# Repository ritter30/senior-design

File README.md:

# G.A.I.N.S Team 19
Cameron Williams \
Max Ritter \
Mark Melvin \
Aidan Leib

## Documentation

All documentation for the project is located in [`./docs`](./docs/).

Hyperlinks to frequently used:

- [Git Commands Cheat Sheet](./docs/git_cheatsheet.md)
- etc...

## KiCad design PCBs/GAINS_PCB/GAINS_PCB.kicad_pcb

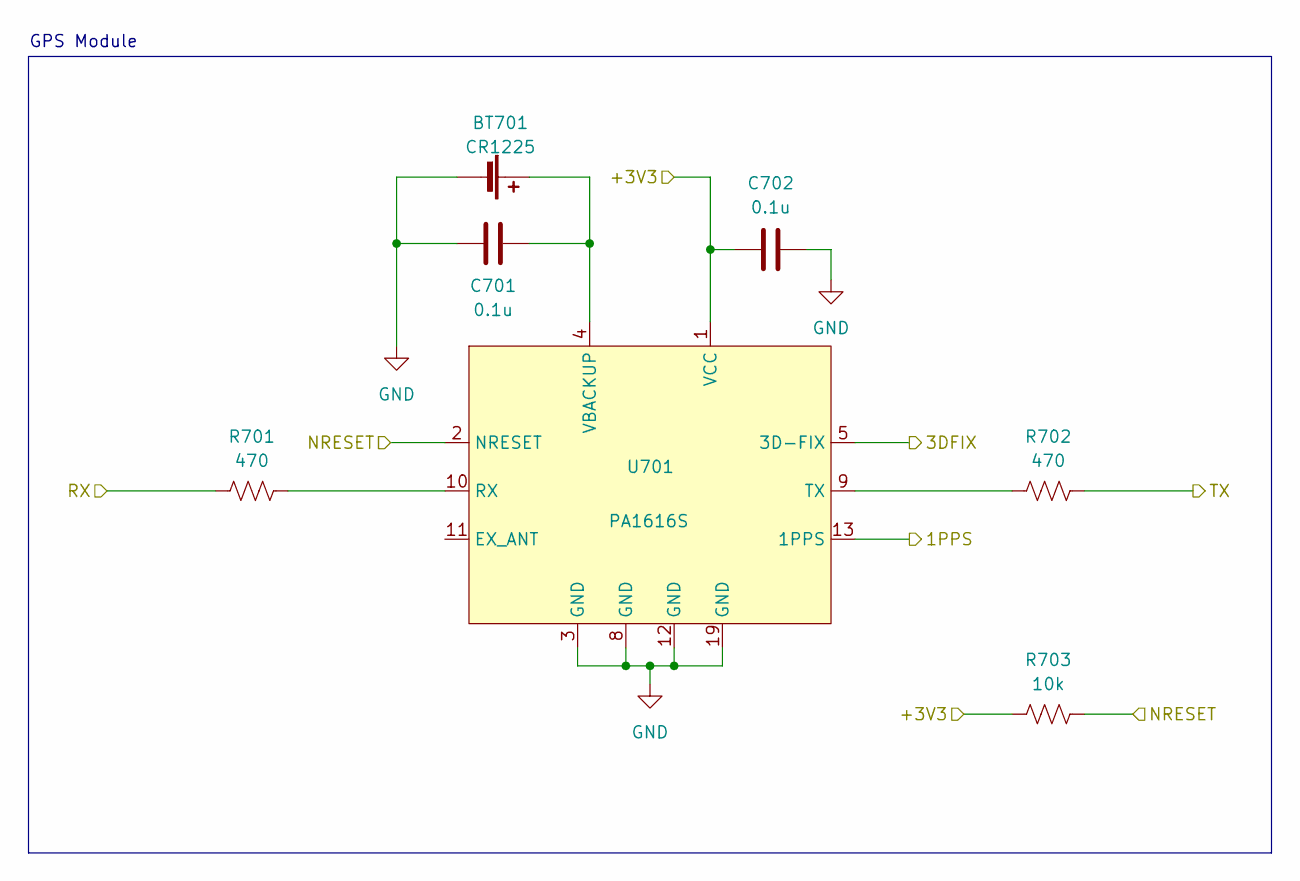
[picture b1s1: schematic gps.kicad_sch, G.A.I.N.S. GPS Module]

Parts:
BT701: CR1225; Battery_Panasonic_CR1220-VCN_Vertical_CircularHoles
C701, C702: 0.1u; C_0805_2012Metric_Pad1.18x1.45mm_HandSolder
R701, R702: 470; R_0805_2012Metric_Pad1.20x1.40mm_HandSolder
R703: 10k; R_0805_2012Metric_Pad1.20x1.40mm_HandSolder
U701: PA1616S

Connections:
/GPS/1PPS: U701.13 (1PPS); also elsewhere on the board
/GPS/3DFIX: U701.5 (3D-FIX); also elsewhere on the board
/GPS/+3V3: C702.1, R703.1, U701.1 (VCC); also elsewhere on the board
/GPS/NRESET: R703.2, U701.2 (NRESET); also elsewhere on the board
/GPS/RX: R701.1; also elsewhere on the board
/GPS/TX: R702.1; also elsewhere on the board
GND: BT701.2 (-), C701.1, C702.2, U701.3 (GND), U701.8 (GND), U701.12 (GND), U701.19 (GND); also elsewhere on the board
unnamed: BT701.1 (+), C701.2, U701.4 (VBACKUP)
unnamed: R701.2, U701.10 (RX)
unnamed: R702.2, U701.9 (TX)

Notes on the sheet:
GPS Module

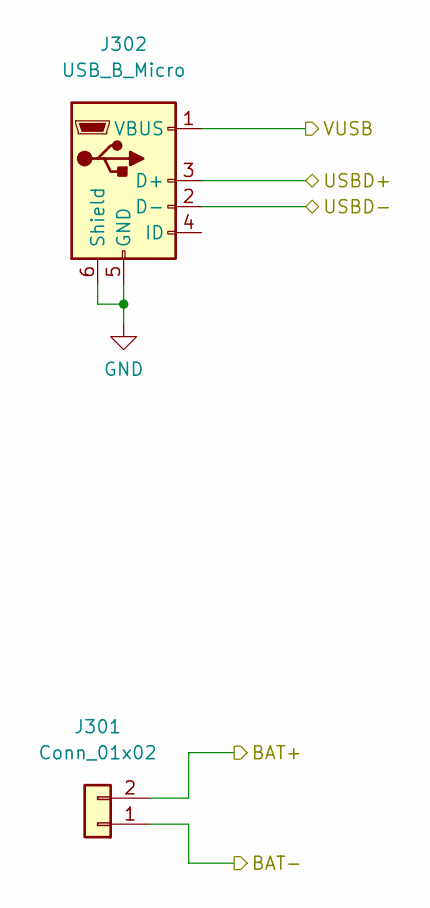
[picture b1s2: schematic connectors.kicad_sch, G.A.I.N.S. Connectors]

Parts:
J301: Conn_01x02; JST_GH_BM02B-GHS-TBT_1x02-1MP_P1.25mm_Vertical
J302: USB_B_Micro; USB_Micro-B_Amphenol_10104110_Horizontal

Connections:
/Connectors/BAT+: J301.2; also elsewhere on the board
/Connectors/BAT-: J301.1
/Connectors/USBD+: J302.3 (D+); also elsewhere on the board
/Connectors/USBD-: J302.2 (D-); also elsewhere on the board
/Connectors/VUSB: J302.1 (VBUS); also elsewhere on the board
GND: J302.5 (GND), J302.6 (Shield); also elsewhere on the board

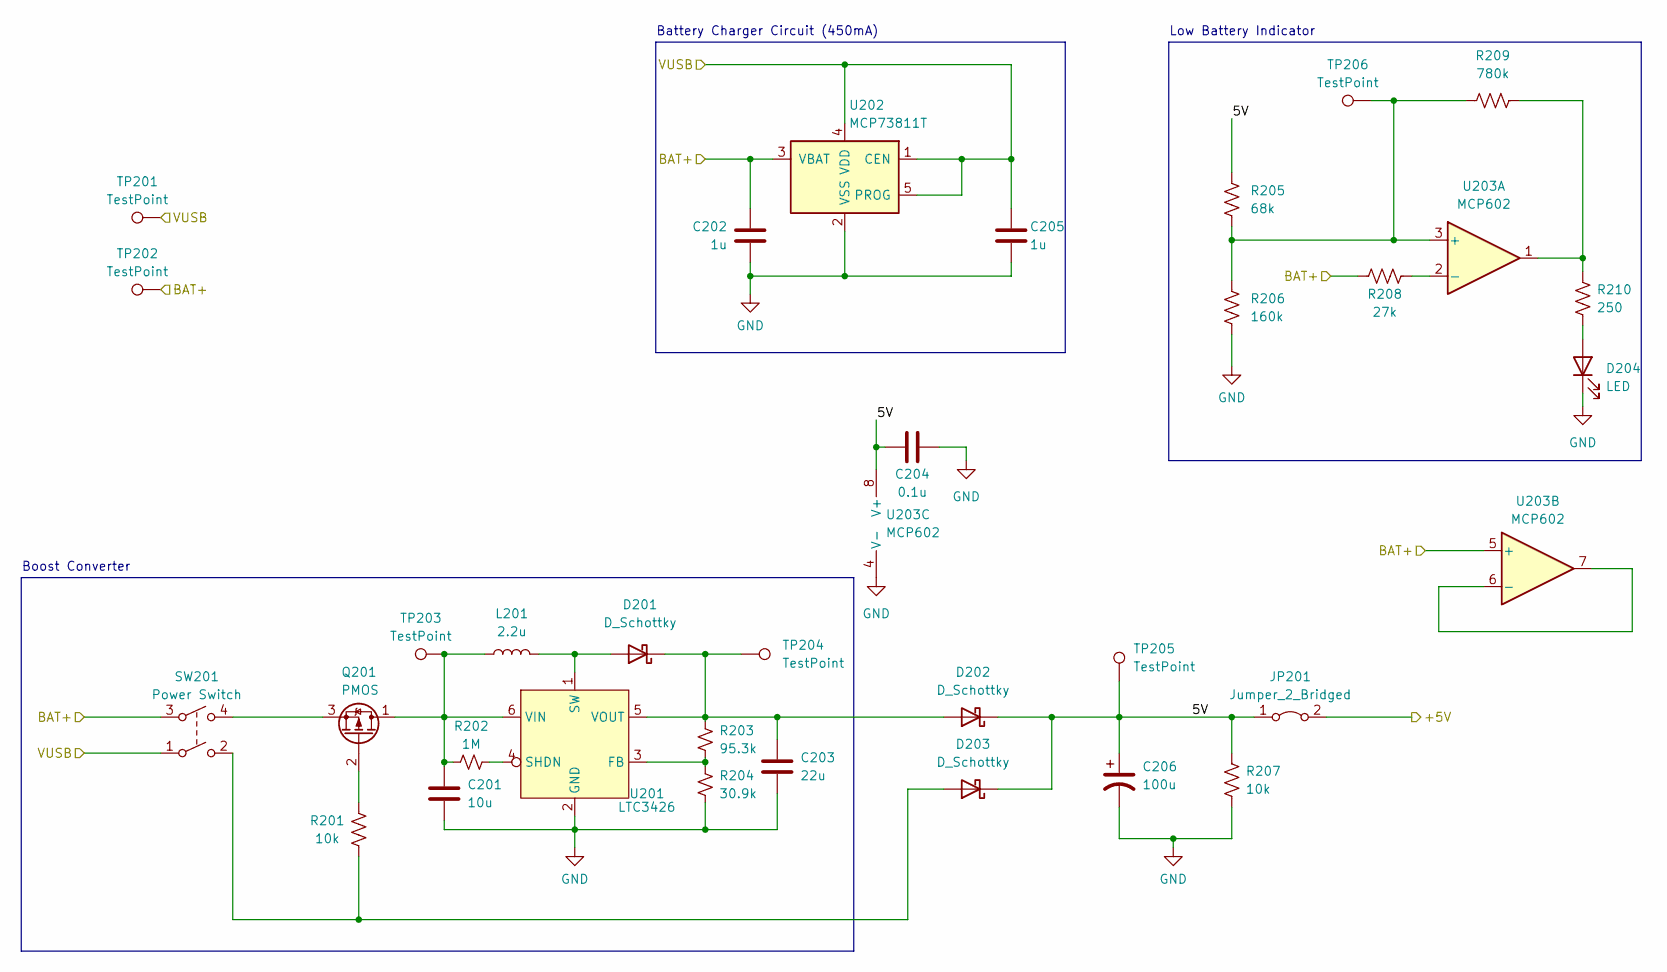
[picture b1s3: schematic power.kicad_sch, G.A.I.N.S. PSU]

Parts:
C201: 10u; C_0805_2012Metric_Pad1.18x1.45mm_HandSolder
C202, C205: 1u; C_0805_2012Metric_Pad1.18x1.45mm_HandSolder
C203: 22u; CP_Radial_D5.0mm_P2.00mm
C204: 0.1u; C_0805_2012Metric_Pad1.18x1.45mm_HandSolder
C206: 100u; CP_Radial_D10.0mm_P5.00mm
D201, D202, D203: D_Schottky; D_DO-41_SOD81_P10.16mm_Horizontal
D204: LED; LED_D5.0mm
JP201: Jumper_2_Bridged; SolderJumper-2_P1.3mm_Open_Pad1.0x1.5mm
L201: 2.2u; L_Radial_D8.7mm_P5.00mm_Fastron_07HCP
Q201: PMOS; TO-220-3_Vertical
R201, R207: 10k; R_0805_2012Metric_Pad1.20x1.40mm_HandSolder
R202: 1M; R_0805_2012Metric_Pad1.20x1.40mm_HandSolder
R203: 95.3k; R_0805_2012Metric_Pad1.20x1.40mm_HandSolder
R204: 30.9k; R_0805_2012Metric_Pad1.20x1.40mm_HandSolder
R205: 68k; R_0805_2012Metric_Pad1.20x1.40mm_HandSolder
R206: 160k; R_0805_2012Metric_Pad1.20x1.40mm_HandSolder
R208: 27k; R_0805_2012Metric_Pad1.20x1.40mm_HandSolder
R209: 780k; R_0805_2012Metric_Pad1.20x1.40mm_HandSolder
R210: 250; R_0805_2012Metric_Pad1.20x1.40mm_HandSolder
SW201: Power Switch
TP201, TP202, TP203, TP204, TP205, TP206: TestPoint; PinHeader_1x01_P1.27mm_Vertical
U201: LTC3426; TSOT-23-6_HandSoldering
U202: MCP73811T; SOT-23-5_HandSoldering
U203: MCP602; DIP-8_W7.62mm_Socket

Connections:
/Connectors/BAT+: C202.1, R208.1, SW201.3, TP202.1, U202.3 (VBAT), U203.5 (+); also elsewhere on the board
/Connectors/VUSB: C205.1, SW201.1, TP201.1, U202.1 (CEN), U202.4 (VDD), U202.5 (PROG); also elsewhere on the board
/Power/5V: C204.1, C206.1, D202.1 (K), D203.1 (K), JP201.1 (A), R205.2, R207.1, TP205.1, U203.8 (V+)
/Power/+5V: JP201.2 (B); also elsewhere on the board
GND: C201.2, C202.2, C203.2, C204.2, C205.2, C206.2, D204.1 (K), R204.2, R206.1, R207.2, U201.2 (GND), U202.2 (VSS), U203.4 (V-); also elsewhere on the board
unnamed: D201.2 (A), L201.2, U201.1 (SW)
unnamed: C203.1, D201.1 (K), D202.2 (A), R203.1, TP204.1, U201.5 (VOUT)
unnamed: D203.2 (A), R201.1, SW201.2
unnamed: D204.2 (A), R210.2
unnamed: C201.1, L201.1, Q201.1 (D), R202.1, TP203.1, U201.6 (VIN)
unnamed: Q201.2 (G), R201.2
unnamed: Q201.3 (S), SW201.4
unnamed: R209.2, R210.1, U203.1
unnamed: R203.2, R204.1, U201.3 (FB)
unnamed: R202.2, U201.4 (SHDN)
unnamed: R205.1, R206.2, R209.1, TP206.1, U203.3 (+)
unnamed: R208.2, U203.2 (-)
unnamed: U203.6 (-), U203.7

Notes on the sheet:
Boost Converter
Low Battery Indicator
Battery Charger Circuit (450mA)

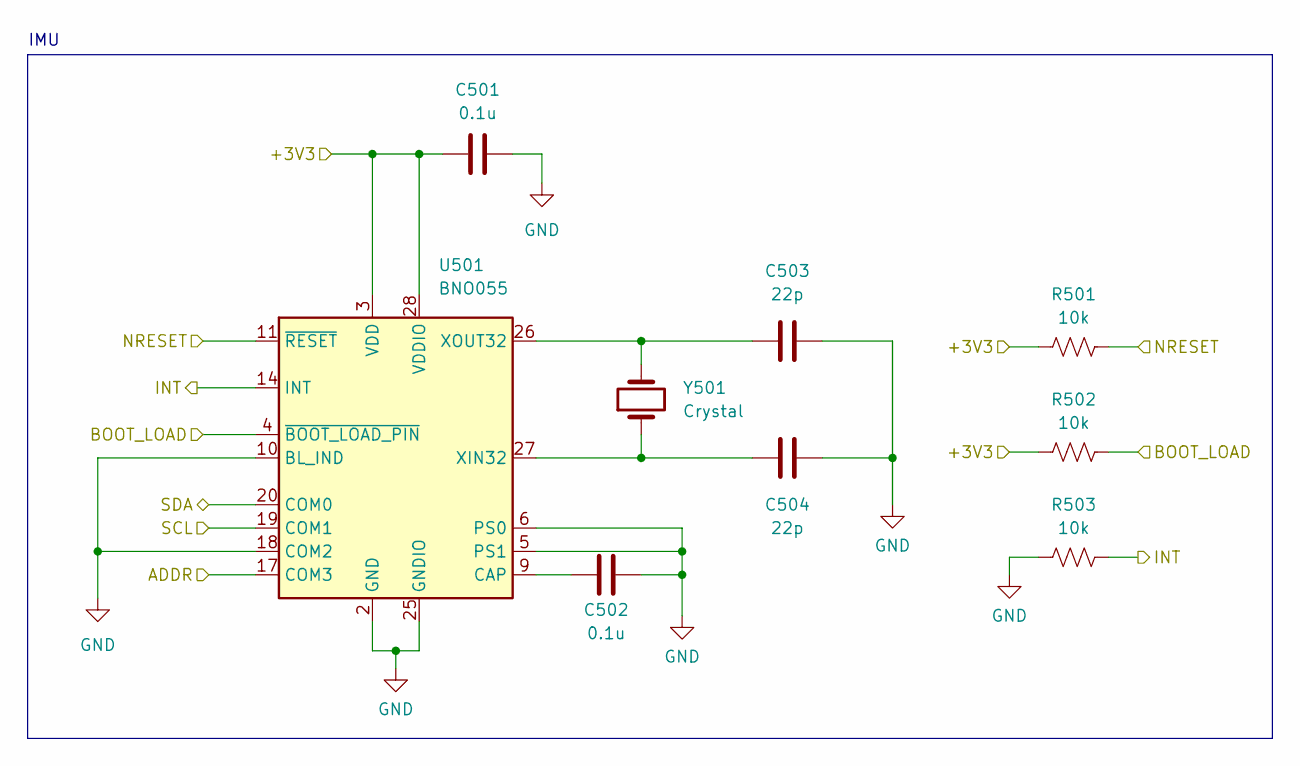
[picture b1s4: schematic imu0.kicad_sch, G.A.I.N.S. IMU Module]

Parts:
C501, C502: 0.1u; C_0805_2012Metric_Pad1.18x1.45mm_HandSolder
C503, C504: 22p; C_0805_2012Metric_Pad1.18x1.45mm_HandSolder
R501, R502, R503: 10k; R_0805_2012Metric_Pad1.20x1.40mm_HandSolder
U501: BNO055; LGA-28_5.2x3.8mm_P0.5mm
Y501: Crystal; Crystal_DS26_D2.0mm_L6.0mm_Vertical

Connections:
/GPS/+3V3: C501.1, R501.1, R502.1, U501.3 (VDD), U501.28 (VDDIO); also elsewhere on the board
/IMU0/BOOT_LOAD: R502.2, U501.4 (~BOOT_LOAD_PIN); also elsewhere on the board
/IMU0/INT: R503.2, U501.14 (INT); also elsewhere on the board
/IMU0/NRESET: R501.2, U501.11 (~RESET); also elsewhere on the board
/IMU0/SCL: U501.19 (COM1); also elsewhere on the board
/IMU0/SDA: U501.20 (COM0); also elsewhere on the board
GND: C501.2, C502.2, C503.1, C504.1, R503.1, U501.2 (GND), U501.5 (PS1), U501.6 (PS0), U501.10 (BL_IND), U501.15 (GNDIO), U501.16 (GNDIO), U501.18 (COM2), U501.25 (GNDIO); also elsewhere on the board
unnamed: C502.1, U501.9 (CAP)
unnamed 45: U501.17 (COM3); also elsewhere on the board
unnamed: C504.2, U501.27 (XIN32), Y501.1
unnamed: C503.2, U501.26 (XOUT32), Y501.2

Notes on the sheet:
IMU

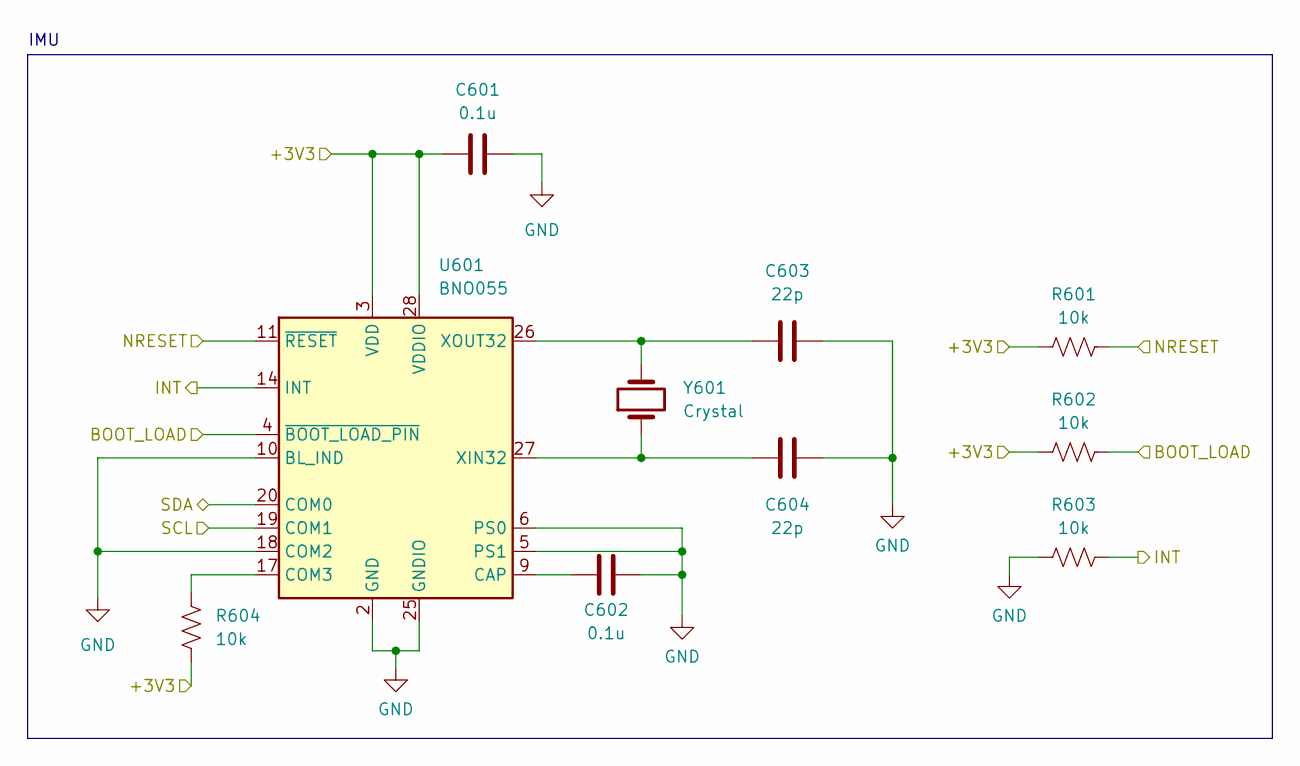
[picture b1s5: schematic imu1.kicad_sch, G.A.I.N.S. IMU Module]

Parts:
C601, C602: 0.1u; C_0805_2012Metric_Pad1.18x1.45mm_HandSolder
C603, C604: 22p; C_0805_2012Metric_Pad1.18x1.45mm_HandSolder
R601, R602, R603, R604: 10k; R_0805_2012Metric_Pad1.20x1.40mm_HandSolder
U601: BNO055; LGA-28_5.2x3.8mm_P0.5mm
Y601: Crystal; Crystal_DS26_D2.0mm_L6.0mm_Vertical

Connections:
/GPS/+3V3: C601.1, R601.1, R602.1, R604.2, U601.3 (VDD), U601.28 (VDDIO); also elsewhere on the board
/IMU0/SCL: U601.19 (COM1); also elsewhere on the board
/IMU0/SDA: U601.20 (COM0); also elsewhere on the board
/IMU1/BOOT_LOAD: R602.2, U601.4 (~BOOT_LOAD_PIN); also elsewhere on the board
/IMU1/INT: R603.2, U601.14 (INT); also elsewhere on the board
/IMU1/NRESET: R601.2, U601.11 (~RESET); also elsewhere on the board
GND: C601.2, C602.2, C603.1, C604.1, R603.1, U601.2 (GND), U601.5 (PS1), U601.6 (PS0), U601.10 (BL_IND), U601.15 (GNDIO), U601.16 (GNDIO), U601.18 (COM2), U601.25 (GNDIO); also elsewhere on the board
unnamed: C602.1, U601.9 (CAP)
unnamed: R604.1, U601.17 (COM3)
unnamed: C604.2, U601.27 (XIN32), Y601.1
unnamed: C603.2, U601.26 (XOUT32), Y601.2

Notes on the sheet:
IMU

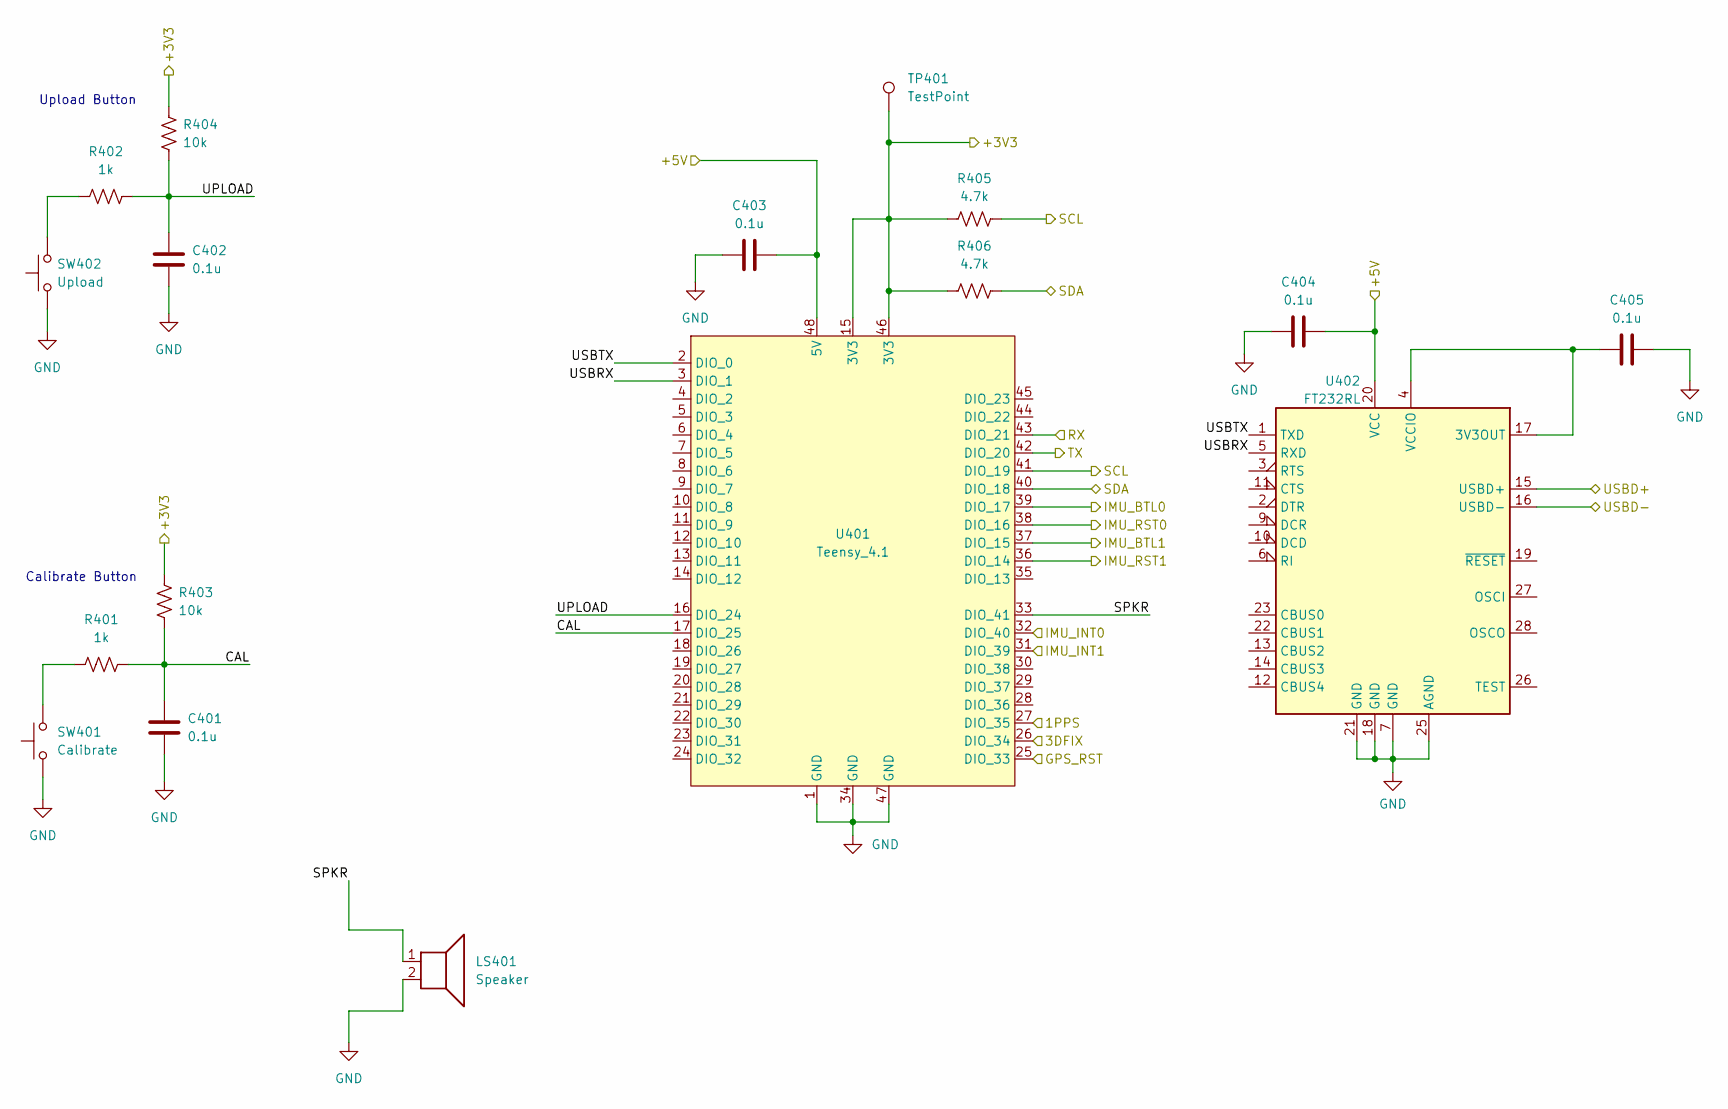
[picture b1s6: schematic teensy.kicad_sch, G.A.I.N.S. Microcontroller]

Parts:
C401, C402, C403, C404, C405: 0.1u; C_0805_2012Metric_Pad1.18x1.45mm_HandSolder
LS401: Speaker; Buzzer_12x9.5RM7.6
R401, R402: 1k; R_0805_2012Metric_Pad1.20x1.40mm_HandSolder
R403, R404: 10k; R_0805_2012Metric_Pad1.20x1.40mm_HandSolder
R405, R406: 4.7k; R_0805_2012Metric_Pad1.20x1.40mm_HandSolder
SW401: Calibrate; SW_PUSH_6mm
SW402: Upload; SW_PUSH_6mm
TP401: TestPoint; PinHeader_1x01_P1.27mm_Vertical
U401: Teensy_4.1; Teensy41
U402: FT232RL; SSOP-28_5.3x10.2mm_P0.65mm

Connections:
/Connectors/USBD+: U402.15 (USBD+); also elsewhere on the board
/Connectors/USBD-: U402.16 (USBD-); also elsewhere on the board
/GPS/1PPS: U401.27 (DIO_35); also elsewhere on the board
/GPS/3DFIX: U401.26 (DIO_34); also elsewhere on the board
/GPS/+3V3: R403.1, R404.1, R405.1, R406.1, TP401.1, U401.15 (3V3), U401.46 (3V3); also elsewhere on the board
/GPS/NRESET: U401.25 (DIO_33); also elsewhere on the board
/GPS/RX: U401.42 (DIO_20); also elsewhere on the board
/GPS/TX: U401.43 (DIO_21); also elsewhere on the board
/IMU0/BOOT_LOAD: U401.39 (DIO_17); also elsewhere on the board
/IMU0/INT: U401.32 (DIO_40); also elsewhere on the board
/IMU0/NRESET: U401.38 (DIO_16); also elsewhere on the board
/IMU0/SCL: R405.2, U401.41 (DIO_19); also elsewhere on the board
/IMU0/SDA: R406.2, U401.40 (DIO_18); also elsewhere on the board
/IMU1/BOOT_LOAD: U401.37 (DIO_15); also elsewhere on the board
/IMU1/INT: U401.31 (DIO_39); also elsewhere on the board
/IMU1/NRESET: U401.36 (DIO_14); also elsewhere on the board
/Power/+5V: C403.2, C404.1, U401.48 (5V), U402.20 (VCC); also elsewhere on the board
/Teensy/CAL: C401.1, R401.2, R403.2, U401.17 (DIO_25)
/Teensy/SPKR: LS401.1, U401.33 (DIO_41)
/Teensy/UPLOAD: C402.1, R402.2, R404.2, U401.16 (DIO_24)
/Teensy/USBRX: U401.3 (DIO_1), U402.5 (RXD)
/Teensy/USBTX: U401.2 (DIO_0), U402.1 (TXD)
GND: C401.2, C402.2, C403.1, C404.2, C405.1, LS401.2, SW401.1, SW402.1, U401.1 (GND), U401.34 (GND), U401.47 (GND), U402.7 (GND), U402.18 (GND), U402.21 (GND), U402.25 (AGND); also elsewhere on the board
unnamed: R401.1, SW401.2
unnamed: R402.1, SW402.2
unnamed: C405.2, U402.4 (VCCIO), U402.17 (3V3OUT)

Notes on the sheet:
Calibrate Button
Upload Button

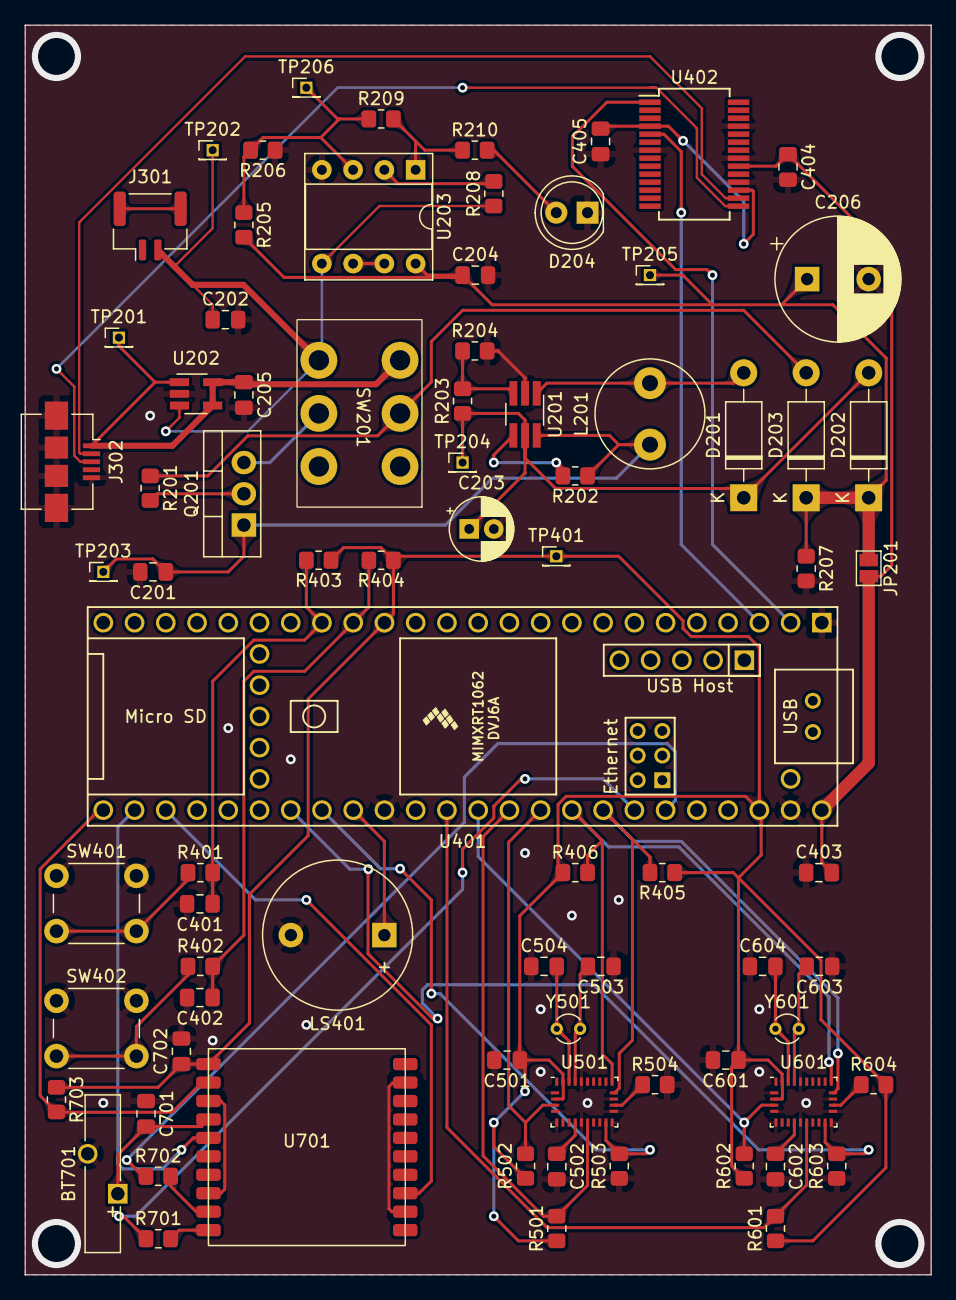
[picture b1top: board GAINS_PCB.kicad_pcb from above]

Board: 2 copper layers, 73.7 x 101.6 mm, 79 parts (0 on the bottom side), 53 nets.

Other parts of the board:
R504: 10k; R_0805_2012Metric_Pad1.20x1.40mm_HandSolder

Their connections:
GND: R504.2; also elsewhere on the board
unnamed 45: R504.1; also elsewhere on the board

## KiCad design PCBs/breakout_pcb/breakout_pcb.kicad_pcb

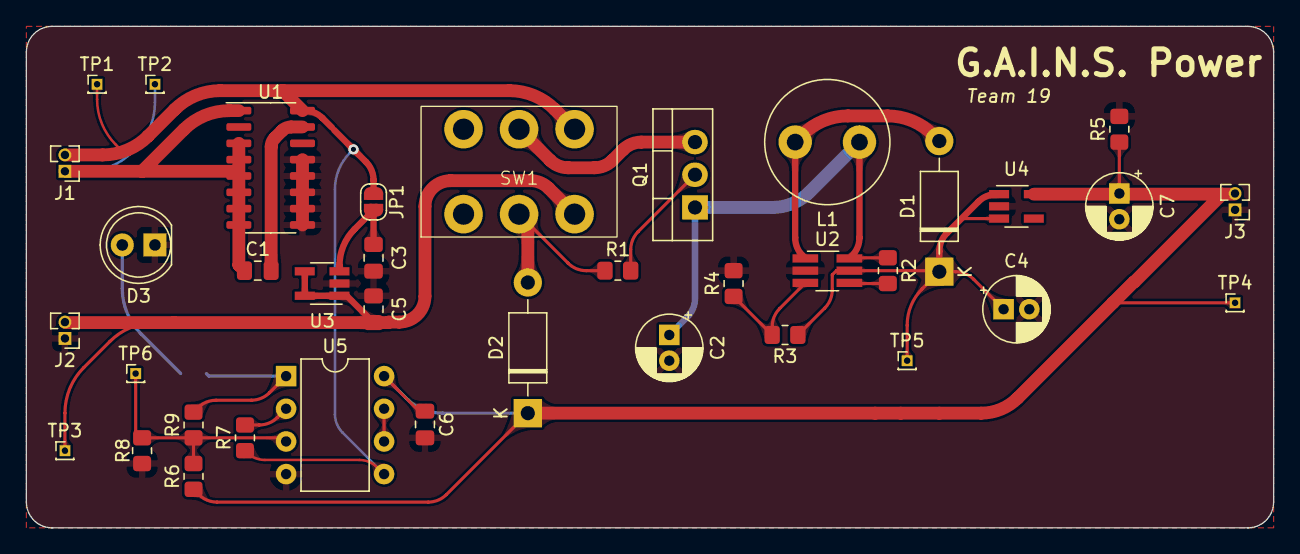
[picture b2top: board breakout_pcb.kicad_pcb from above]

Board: 2 copper layers, 97.0 x 39.0 mm, 38 parts (1 on the bottom side), 20 nets.

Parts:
C1, C6: 0.1u; C_0805_2012Metric_Pad1.18x1.45mm_HandSolder
C2: 10u; CP_Radial_D5.0mm_P2.00mm
C3, C5: 1u; C_0805_2012Metric_Pad1.18x1.45mm_HandSolder
C4: 22u; CP_Radial_D5.0mm_P2.00mm
C7: 82u; CP_Radial_D5.0mm_P2.00mm
D1, D2: 1N5819; D_DO-41_SOD81_P10.16mm_Horizontal
D3: Red LED; LED_D5.0mm
J1, J2, J3: Conn_01x02_Socket; PinHeader_1x02_P1.27mm_Vertical
JP1: Jumper_2_Open; SolderJumper-2_P1.3mm_Open_RoundedPad1.0x1.5mm
L1: 2.2u; L_Radial_D9.5mm_P5.00mm_Fastron_07HVP
Q1: IRF9630; TO-220-3_Vertical
R1, R5, R6: 10k; R_0805_2012Metric_Pad1.20x1.40mm_HandSolder
R2: 1M; R_0805_2012Metric_Pad1.20x1.40mm_HandSolder
R3: 95.3k; R_0805_2012Metric_Pad1.20x1.40mm_HandSolder
R4: 30.9k; R_0805_2012Metric_Pad1.20x1.40mm_HandSolder
R7: 1k; R_0805_2012Metric_Pad1.20x1.40mm_HandSolder
R8: 30k; R_0805_2012Metric_Pad1.20x1.40mm_HandSolder
R9: 100k; R_0805_2012Metric_Pad1.20x1.40mm_HandSolder
R10: 250; R_0805_2012Metric_Pad1.20x1.40mm_HandSolder
SW1: SW_DPST; Power Switch
TP1, TP2, TP3, TP4, TP5, TP6: TestPoint; PinHeader_1x01_P1.00mm_Vertical
U1: UCC39562; SOIC-16_3.9x9.9mm_P1.27mm
U2: LTC3426; TSOT-23-6_HandSoldering
U3: MCP73811T; SOT-23-5_HandSoldering
U4: MAX40200AUK; SOT-23-5_HandSoldering
U5: MCP602; DIP-8_W7.62mm

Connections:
/+5V: C6.1, C7.1, D2.1 (K), J3.2, R5.1, R6.1, TP4.1, U4.5 (OUT), U5.8 (V+)
/BAT+: J1.2, JP1.1 (A), R7.1, SW1.3, TP1.1, U1.16 (PACK+), U5.5 (+)
/BAT-: C1.1, J1.1, TP2.1, U1.1 (TCLK), U1.3 (BNEG), U1.4 (BNEG), U1.5 (BNEG), U1.6 (BNEG), U1.7 (BNEG), U1.8 (BNEG)
/VUSB: C5.1, J2.2, SW1.1, TP3.1, U3.1 (CEN), U3.4 (VDD), U3.5 (PROG)
GND: C2.2, C3.2, C4.2, C5.2, C6.2, C7.2, D3.1 (K), J2.1, J3.1, R4.2, R5.2, R8.2, U1.9 (PACK-), U1.10 (PACK-), U1.11 (PACK-), U1.12 (PACK-), U1.13 (PACK-), U2.2 (GND), U3.2 (VSS), U4.2 (GND), U5.4 (V-)
unnamed: D1.2 (A), L1.2, U2.1 (SW)
unnamed: C4.1, D1.1 (K), R3.1, TP5.1, U2.5 (VOUT), U4.1 (VDD), U4.3 (EN)
unnamed: D2.2 (A), R1.1, SW1.2
unnamed: D3.2 (A), R10.2
unnamed: C3.1, JP1.2 (B), U3.3 (VBAT)
unnamed: C2.1, L1.1, Q1.1 (D), R2.1, U2.6 (VIN)
unnamed: Q1.2 (G), R1.2
unnamed: Q1.3 (S), SW1.4
unnamed: R9.2, R10.1, U5.1
unnamed: C1.2, U1.15 (CBPS)
unnamed: R3.2, R4.1, U2.3 (FB)
unnamed: R2.2, U2.4 (SHDN)
unnamed: R6.2, R8.1, R9.1, TP6.1, U5.3 (+)
unnamed: R7.2, U5.2 (-)
unnamed: U5.6 (-), U5.7

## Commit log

2024-01-11 testing repo access
2024-01-11 test two for git scripting
2024-01-13 added mermaid.js code for the activity diagram
2024-01-25 added
2024-01-25 adding documentation
2024-01-25 Added PCB
2024-01-26 Initial PCB Schematic
2024-01-26 Teensy and IMU PCB Schematics
2024-01-28 PCB Schematic Updates
2024-01-30 minor changes
2024-01-30 updated git cheatsheet
2024-01-30 Fixing Schematic
2024-02-01 PCB Updates
2024-02-02 removing schematic from branch 'aidan'
2024-02-02 introduction to building the application, added styling files and data
2024-02-04 Micro code
2024-02-05 Attempting live data updates
2024-02-05 Working live update mvp App
2024-02-08 Updated battery protection circuit
2024-02-08 Added the breakout board PCB
2024-02-08 init for pyserial implementation
2024-02-08 almost forgot updated gitignore
2024-02-09 Worked on PCB
2024-02-09 updated power breakout board
2024-02-09 Final Breakout Board PCB
2024-02-09 updated .gitignore
2024-02-12 build gerber files for ordering PCB
2024-02-13 playing with plotting geospatial data
2024-02-14 negiligible updates to app
2024-02-14 updated gitignore
2024-02-15 pushing working tree, only changed app print()
2024-02-15 added kalman filter script to play with
2024-02-17 Deleted battery protectection circuit and ideal diode
2024-02-17 Changed resistor values for low battery indicator
2024-02-19 fleshed out 1D kalman filter example --> next apply to 3D
2024-02-20 midterm demo app working checkpoint
2024-02-20 additional mods to app for midterm demo
2024-02-20 editted serial in
2024-02-20 post midterm demo
2024-02-27 notes on kf.py
2024-03-04 GAINS PCB Rev 1
2024-03-05 attempting multivariate kalman filter in python
2024-03-05 resaved kf.py from last commit
2024-03-21 i think i figured out the matrices for our kalman filter implementation. Still need to look into some shape differences and the initial P matrix (state cov).
2024-03-26 kalman filter designed, want to test with IMU and GPS data now (sensor fusion)
2024-04-02 data cleaning from max's collection to test kalman filter. need to input imu and gps into kf next.
2024-04-02 temp commit to switch branch
2024-04-05 Working fused kalman filter. Need to figure out good ways to visualize results.
2024-04-09 added tkinter app in case it's easier to plot live
2024-04-13 quick save
2024-04-13 Adding new data
2024-04-13 Added arduino folder structure
2024-04-13 beautified plots for lat and lon
2024-04-13 updated .gitignore file
2024-04-13 another update to .gitignore
2024-04-17 addedd c++ kalman filter
2024-04-17 starting to translate KF to c++
2024-04-17 moving kalman filter to micro code location
2024-04-18 more edits to c++ kalman filter, moving on to focusing hte UI
2024-04-18 matplot animation working
2024-04-23 good enough UI i think
2024-04-23 working app with orientation, not pretty, lmao'
2024-04-23 edits to run as jupyter notebook, not importing kf
2024-04-26 new photos
